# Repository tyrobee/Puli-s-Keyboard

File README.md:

# Puli-s-Keyboard
I always wanted to get a keyboard but being a person who love making stuff on thier own instead of getting them so i started building the keyboard

i built the keyboard with 81 keys and a rotary encoder w a raspberrypi pico as the microcontroller and uses the open source  QMK firmware.It can also be called as a 78% Keyboard :))

## Schematics

## PCB

## CAD

## Assembly

## BOM

| Component | Purpose | Qty | Unit Cost ($) | Total ($) | Link | Distributor |
|----------|--------|-----|--------------|-----------|------|------------|
| USB A Type to Micro USB B Cable | cable | 1 | 0.41| 0.41 | https://robocraze.com/products/usb-to-micro-usb-cable?variant=40192442007705 | Robu |
| female berg pins | connectors | 3 | 0.28 | 0.28 | https://robocraze.com/products/40x1-female-berg-strip?_pos=5&_sid=7dbcf9cbf&_ss=r | robocraze |
| Raspberry Pi Pico | microcontroller | 1 | 4.21 | 4.21 | https://robocraze.com/products/raspberry-pi-pico?variant=40194204860569&country=IN&currency=INR&utm_medium=product_sync&utm_source=google&utm_content=sag_organic&utm_campaign=sag_organic&campaignid=17937704573&adgroupid=&keyword=&device=c&gad_source=1&gad_campaignid=17931338845&gbraid=0AAAAADgHQvYy5ICv2k3FTsuabMyJ0fSu1&gclid=Cj0KCQjw2MbPBhCSARIsAP3jP9yaVdQ3fHISi06ooGjh3m9m9IB-P7hm8X7wTPkkNGJwUihs7WsVG1QaAuErEALw_wcB | Robocraze |
| 4x10 Enkeysphere Cherry Profile PBT Keycaps | keycaps | 1 | 21.17 | 21.17 | https://stackskb.com/store/hemisphere-keycaps/| StacksKB |
| Switches (Akko Creamy Cyan) | keys | 90 | 0.30 | 27.37 | https://stackskb.com/store/akko-creamy-cyan-switch-pack-of-45-pre-order/ | StacksKB |
|pcb | pcb | 1 |42.64 |42.64 | - | JLCPCB |

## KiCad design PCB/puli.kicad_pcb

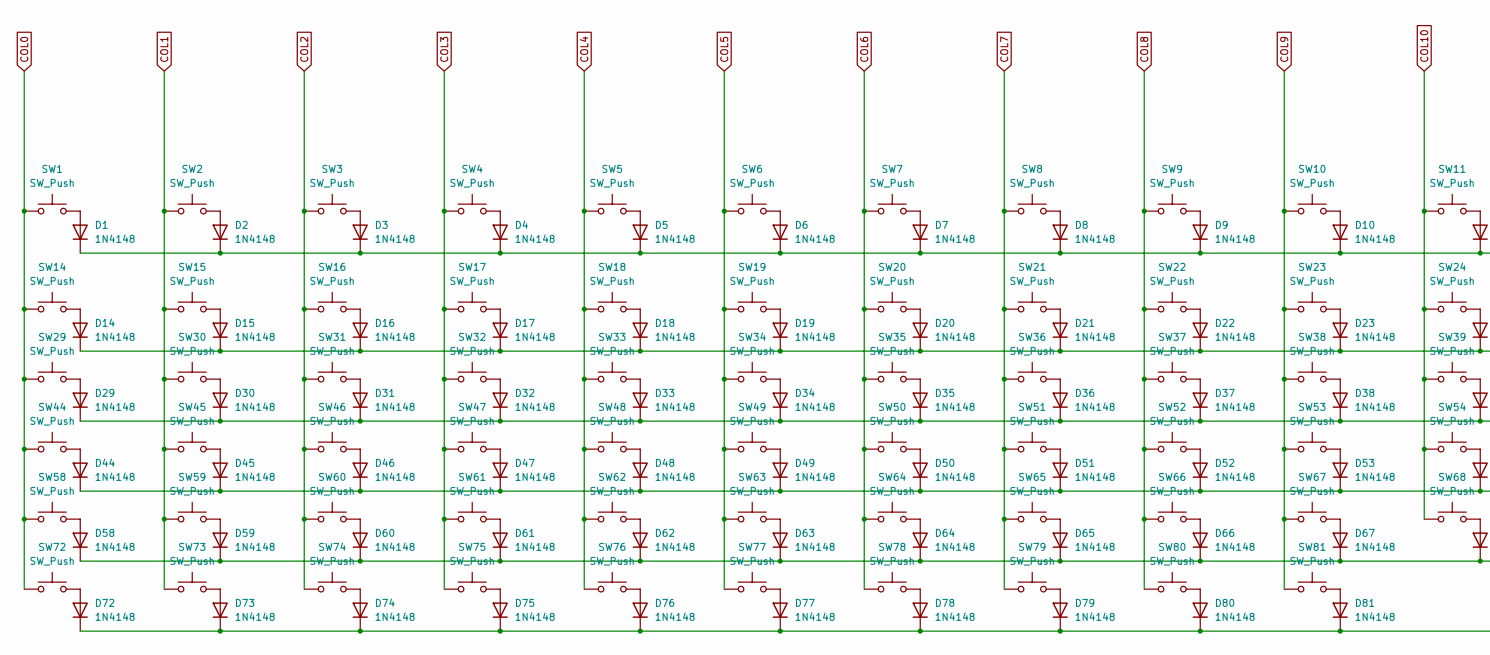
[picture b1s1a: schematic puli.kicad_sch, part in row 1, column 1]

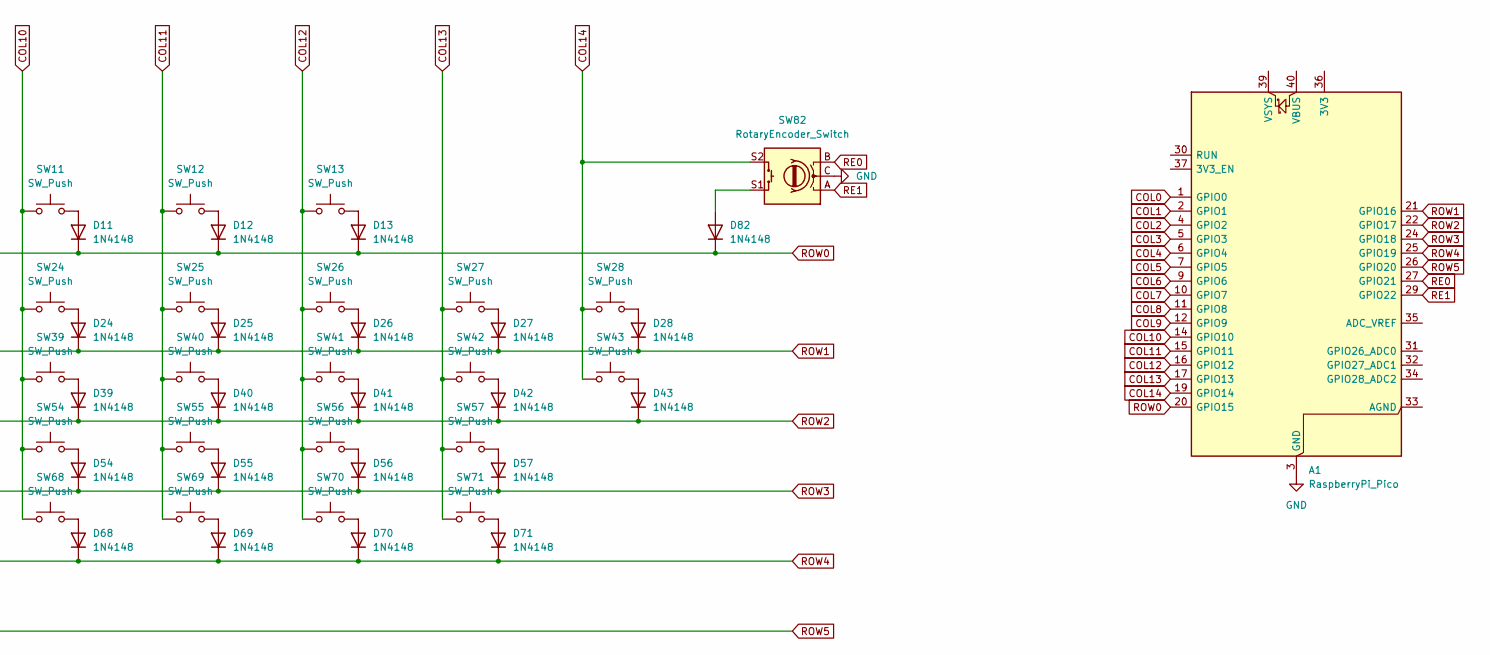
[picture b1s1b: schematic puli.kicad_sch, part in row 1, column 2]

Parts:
A1: RaspberryPi_Pico; RaspberryPi_Pico_Common_Unspecified
D1, D2, D3, D4, D5, D6, D7, D8, D9, D10, D11, D12, D13, D14, D15, D16, D17, D18, D19, D20, D21, D22, D23, D24, D25, D26, D27, D28, D29, D30, D31, D32, D33, D34, D35, D36, D37, D38, D39, D40, D41, D42, D43, D44, D45, D46, D47, D48, D49, D50, D51, D52, D53, D54, D55, D56, D57, D58, D59, D60, D61, D62, D63, D64, D65, D66, D67, D68, D69, D70, D71, D72, D73, D74, D75, D76, D77, D78, D79, D80, D81, D82: 1N4148; D_DO-35_SOD27_P7.62mm_Horizontal
SW1, SW2, SW3, SW4, SW5, SW6, SW7, SW8, SW9, SW10, SW11, SW12, SW13, SW14, SW15, SW16, SW17, SW18, SW19, SW20, SW21, SW22, SW23, SW24, SW25, SW26, SW28, SW30, SW31, SW32, SW33, SW34, SW35, SW36, SW37, SW38, SW39, SW40, SW41, SW43, SW45, SW46, SW47, SW48, SW49, SW50, SW51, SW52, SW53, SW54, SW55, SW57, SW59, SW60, SW61, SW62, SW63, SW64, SW65, SW66, SW67, SW68, SW70, SW71, SW76, SW77, SW78, SW79, SW80, SW81: SW_Push; SW_Cherry_MX_1.00u_PCB
SW27: SW_Push; SW_Cherry_MX_2.00u_PCB
SW29, SW42: SW_Push; SW_Cherry_MX_1.50u_PCB
SW44, SW69: SW_Push; SW_Cherry_MX_1.75u_PCB
SW56, SW58: SW_Push; SW_Cherry_MX_2.25u_PCB
SW72, SW73, SW74: SW_Push; SW_Cherry_MX_1.25u_PCB
SW75: SW_Push; SW_Cherry_MX_6.25u_PCB
SW82: RotaryEncoder_Switch; RotaryEncoder_Alps_EC11E-Switch_Vertical_H20mm

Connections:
COL0: A1.1 (GPIO0), SW1.1, SW14.1, SW29.1, SW44.1, SW58.1, SW72.1
COL1: A1.2 (GPIO1), SW2.1, SW15.1, SW30.1, SW45.1, SW59.1, SW73.1
COL2: A1.4 (GPIO2), SW3.1, SW16.1, SW31.1, SW46.1, SW60.1, SW74.1
COL3: A1.5 (GPIO3), SW4.1, SW17.1, SW32.1, SW47.1, SW61.1, SW75.1
COL4: A1.6 (GPIO4), SW5.1, SW18.1, SW33.1, SW48.1, SW62.1, SW76.1
COL5: A1.7 (GPIO5), SW6.1, SW19.1, SW34.1, SW49.1, SW63.1, SW77.1
COL6: A1.9 (GPIO6), SW7.1, SW20.1, SW35.1, SW50.1, SW64.1, SW78.1
COL7: A1.10 (GPIO7), SW8.1, SW21.1, SW36.1, SW51.1, SW65.1, SW79.1
COL8: A1.11 (GPIO8), SW9.1, SW22.1, SW37.1, SW52.1, SW66.1, SW80.1
COL9: A1.12 (GPIO9), SW10.1, SW23.1, SW38.1, SW53.1, SW67.1, SW81.1
COL10: A1.14 (GPIO10), SW11.1, SW24.1, SW39.1, SW54.1, SW68.1
COL11: A1.15 (GPIO11), SW12.1, SW25.1, SW40.1, SW55.1, SW69.1
COL12: A1.16 (GPIO12), SW13.1, SW26.1, SW41.1, SW56.1, SW70.1
COL13: A1.17 (GPIO13), SW27.1, SW42.1, SW57.1, SW71.1
COL14: A1.19 (GPIO14), SW28.1, SW43.1, SW82.S2
GND: A1.3 (GND), A1.8 (GND), A1.13 (GND), A1.18 (GND), A1.23 (GND), A1.28 (GND), A1.38 (GND), SW82.C
unnamed: D1.2 (A), SW1.2
unnamed: D2.2 (A), SW2.2
unnamed: D3.2 (A), SW3.2
unnamed: D4.2 (A), SW4.2
unnamed: D5.2 (A), SW5.2
unnamed: D6.2 (A), SW6.2
unnamed: D7.2 (A), SW7.2
unnamed: D8.2 (A), SW8.2
unnamed: D9.2 (A), SW9.2
unnamed: D10.2 (A), SW10.2
unnamed: D11.2 (A), SW11.2
unnamed: D12.2 (A), SW12.2
unnamed: D13.2 (A), SW13.2
unnamed: D14.2 (A), SW14.2
unnamed: D15.2 (A), SW15.2
unnamed: D16.2 (A), SW16.2
unnamed: D17.2 (A), SW17.2
unnamed: D18.2 (A), SW18.2
unnamed: D19.2 (A), SW19.2
unnamed: D20.2 (A), SW20.2
unnamed: D21.2 (A), SW21.2
unnamed: D22.2 (A), SW22.2
unnamed: D23.2 (A), SW23.2
unnamed: D24.2 (A), SW24.2
unnamed: D25.2 (A), SW25.2
unnamed: D26.2 (A), SW26.2
unnamed: D27.2 (A), SW27.2
unnamed: D28.2 (A), SW28.2
unnamed: D29.2 (A), SW29.2
unnamed: D30.2 (A), SW30.2
unnamed: D31.2 (A), SW31.2
unnamed: D32.2 (A), SW32.2
unnamed: D33.2 (A), SW33.2
unnamed: D34.2 (A), SW34.2
unnamed: D35.2 (A), SW35.2
unnamed: D36.2 (A), SW36.2
unnamed: D37.2 (A), SW37.2
unnamed: D38.2 (A), SW38.2
unnamed: D39.2 (A), SW39.2
unnamed: D40.2 (A), SW40.2
unnamed: D41.2 (A), SW41.2
unnamed: D42.2 (A), SW42.2
unnamed: D43.2 (A), SW43.2
unnamed: D44.2 (A), SW44.2
unnamed: D45.2 (A), SW45.2
unnamed: D46.2 (A), SW46.2
unnamed: D47.2 (A), SW47.2
unnamed: D48.2 (A), SW48.2
unnamed: D49.2 (A), SW49.2
unnamed: D50.2 (A), SW50.2
unnamed: D51.2 (A), SW51.2
unnamed: D52.2 (A), SW52.2
unnamed: D53.2 (A), SW53.2
unnamed: D54.2 (A), SW54.2
unnamed: D55.2 (A), SW55.2
unnamed: D56.2 (A), SW56.2
unnamed: D57.2 (A), SW57.2
unnamed: D58.2 (A), SW58.2
unnamed: D59.2 (A), SW59.2
unnamed: D60.2 (A), SW60.2
unnamed: D61.2 (A), SW61.2
unnamed: D62.2 (A), SW62.2
unnamed: D63.2 (A), SW63.2
unnamed: D64.2 (A), SW64.2
unnamed: D65.2 (A), SW65.2
unnamed: D66.2 (A), SW66.2
unnamed: D67.2 (A), SW67.2
unnamed: D68.2 (A), SW68.2
unnamed: D69.2 (A), SW69.2
unnamed: D70.2 (A), SW70.2
unnamed: D71.2 (A), SW71.2
unnamed: D72.2 (A), SW72.2
unnamed: D73.2 (A), SW73.2
unnamed: D74.2 (A), SW74.2
unnamed: D75.2 (A), SW75.2
unnamed: D76.2 (A), SW76.2
unnamed: D77.2 (A), SW77.2
unnamed: D78.2 (A), SW78.2
unnamed: D79.2 (A), SW79.2
unnamed: D80.2 (A), SW80.2
unnamed: D81.2 (A), SW81.2
unnamed: D82.2 (A), SW82.S1
RE0: A1.27 (GPIO21), SW82.B
RE1: A1.29 (GPIO22), SW82.A
ROW0: A1.20 (GPIO15), D1.1 (K), D2.1 (K), D3.1 (K), D4.1 (K), D5.1 (K), D6.1 (K), D7.1 (K), D8.1 (K), D9.1 (K), D10.1 (K), D11.1 (K), D12.1 (K), D13.1 (K), D82.1 (K)
ROW1: A1.21 (GPIO16), D14.1 (K), D15.1 (K), D16.1 (K), D17.1 (K), D18.1 (K), D19.1 (K), D20.1 (K), D21.1 (K), D22.1 (K), D23.1 (K), D24.1 (K), D25.1 (K), D26.1 (K), D27.1 (K), D28.1 (K)
ROW2: A1.22 (GPIO17), D29.1 (K), D30.1 (K), D31.1 (K), D32.1 (K), D33.1 (K), D34.1 (K), D35.1 (K), D36.1 (K), D37.1 (K), D38.1 (K), D39.1 (K), D40.1 (K), D41.1 (K), D42.1 (K), D43.1 (K)
ROW3: A1.24 (GPIO18), D44.1 (K), D45.1 (K), D46.1 (K), D47.1 (K), D48.1 (K), D49.1 (K), D50.1 (K), D51.1 (K), D52.1 (K), D53.1 (K), D54.1 (K), D55.1 (K), D56.1 (K), D57.1 (K)
ROW4: A1.25 (GPIO19), D58.1 (K), D59.1 (K), D60.1 (K), D61.1 (K), D62.1 (K), D63.1 (K), D64.1 (K), D65.1 (K), D66.1 (K), D67.1 (K), D68.1 (K), D69.1 (K), D70.1 (K), D71.1 (K)
ROW5: A1.26 (GPIO20), D72.1 (K), D73.1 (K), D74.1 (K), D75.1 (K), D76.1 (K), D77.1 (K), D78.1 (K), D79.1 (K), D80.1 (K), D81.1 (K)

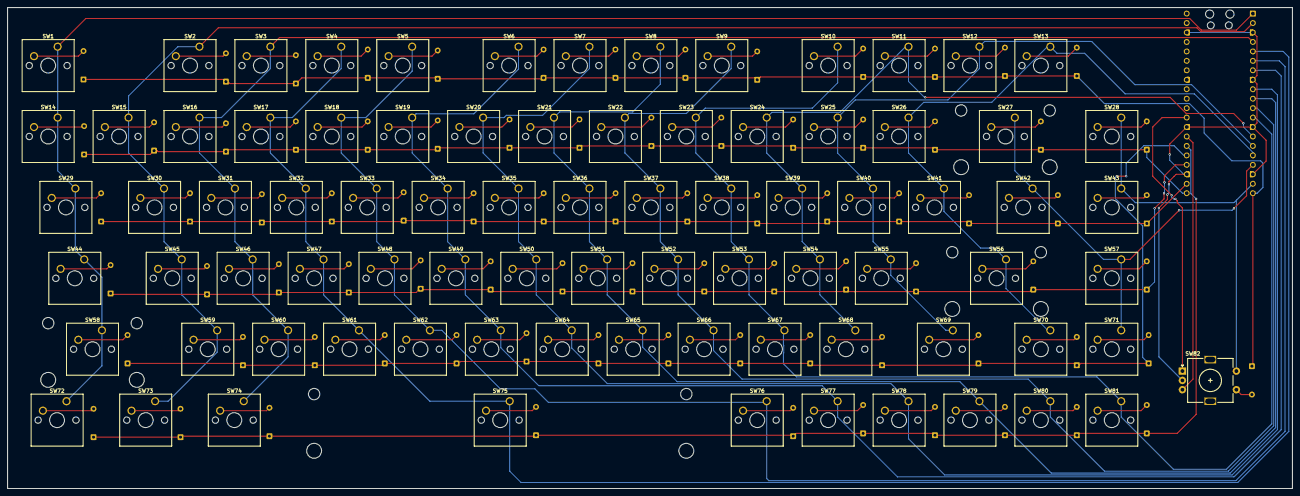
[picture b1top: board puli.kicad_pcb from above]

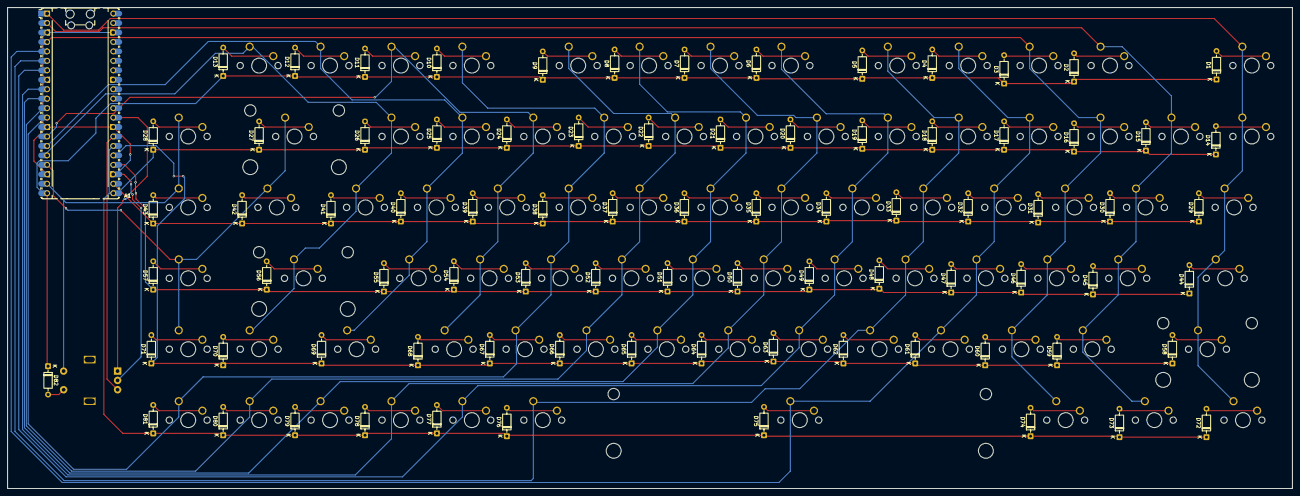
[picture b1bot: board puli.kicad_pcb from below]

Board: 2 copper layers, 345.2 x 129.2 mm, 165 parts (83 on the bottom side), 106 nets.

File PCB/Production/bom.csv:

Designator,Footprint,Quantity,Value,LCSC Part #
A1,RaspberryPi_Pico_Common_Unspecified,1,RaspberryPi_Pico,
"D1, D10, D11, D12, D13, D14, D15, D16, D17, D18, D19, D2, D20, D21, D22, D23, D24, D25, D26, D27, D28, D29, D3, D30, D31, D32, D33, D34, D35, D36, D37, D38, D39, D4, D40, D41, D42, D43, D44, D45, D46, D47, D48, D49, D5, D50, D51, D52, D53, D54, D55, D56, D57, D58, D59, D6, D60, D61, D62, D63, D64, D65, D66, D67, D68, D69, D7, D70, D71, D72, D73, D74, D75, D76, D77, D78, D79, D8, D80, D81, D82, D9",D_DO-35_SOD27_P7.62mm_Horizontal,82,1N4148,
"SW1, SW10, SW11, SW12, SW13, SW14, SW15, SW16, SW17, SW18, SW19, SW2, SW20, SW21, SW22, SW23, SW24, SW25, SW26, SW28, SW3, SW30, SW31, SW32, SW33, SW34, SW35, SW36, SW37, SW38, SW39, SW4, SW40, SW41, SW43, SW45, SW46, SW47, SW48, SW49, SW5, SW50, SW51, SW52, SW53, SW54, SW55, SW57, SW59, SW6, SW60, SW61, SW62, SW63, SW64, SW65, SW66, SW67, SW68, SW7, SW70, SW71, SW76, SW77, SW78, SW79, SW8, SW80, SW81, SW9",SW_Cherry_MX_1.00u_PCB,70,SW_Push,
SW27,SW_Cherry_MX_2.00u_PCB,1,SW_Push,
"SW29, SW42",SW_Cherry_MX_1.50u_PCB,2,SW_Push,
"SW44, SW69",SW_Cherry_MX_1.75u_PCB,2,SW_Push,
"SW56, SW58",SW_Cherry_MX_2.25u_PCB,2,SW_Push,
"SW72, SW73, SW74",SW_Cherry_MX_1.25u_PCB,3,SW_Push,
SW75,SW_Cherry_MX_6.25u_PCB,1,SW_Push,
SW82,RotaryEncoder_Alps_EC11E-Switch_Vertical_H20mm,1,RotaryEncoder_Switch,

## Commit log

2026-04-29 Update README with additional images and sections
    Added images and sections for PCB, CAD, and Assembly.
2026-04-29 Add BOM section with component links to README
2026-04-29 Revise BOM with detailed component costs and links
    Updated the Bill of Materials (BOM) section with detailed component information, including purpose, unit cost, and total cost.
2026-04-29 Add PCB entry to the components list in README
